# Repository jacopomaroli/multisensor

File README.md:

# Multisensor
This is a domotic project aimed to detect presence, temperature and light level in a room and share data with the rest of the ecosystem (e.g. homeassistant)

# Notes
VDO/CS of BME680 should be connected to GND
https://github.com/esphome/issues/issues/2421

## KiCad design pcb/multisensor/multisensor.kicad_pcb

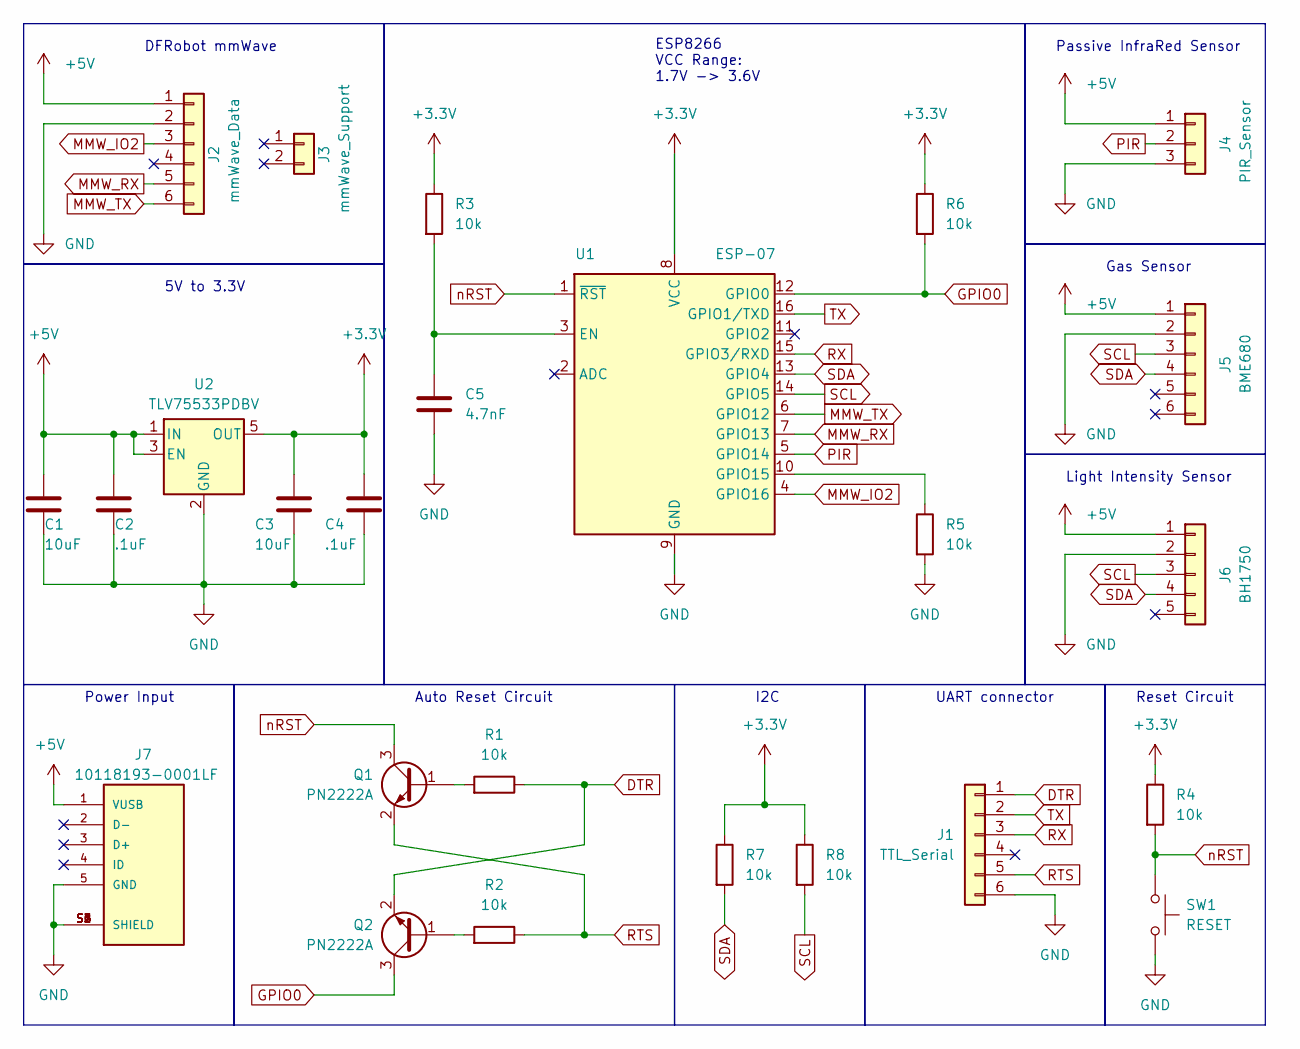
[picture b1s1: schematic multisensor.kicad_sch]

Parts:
C1, C3: 10uF; C_1206_3216Metric; MPN CL31B106KAHNNNE
C2, C4: .1uF; C_1206_3216Metric; MPN C1206C104K5RAC7800
C5: 4.7nF; C_1206_3216Metric; MPN KGM31TR72D472KU
J1: TTL_Serial; PinSocket_1x06_P2.54mm_Vertical; MPN PPPC061LFBN-RC
J2: mmWave_Data; PinSocket_1x06_P2.54mm_Vertical; MPN PPPC061LFBN-RC
J3: mmWave_Support; PinSocket_1x02_P2.54mm_Vertical; MPN PPPC021LFBN-RC
J4: PIR_Sensor; PinSocket_1x03_P2.54mm_Vertical; MPN PPPC031LFBN-RC
J5: BME680; PinSocket_1x06_P2.54mm_Horizontal; MPN PPPC061LGBN-RC
J6: BH1750; PinSocket_1x05_P2.54mm_Horizontal; MPN PPPC051LGBN-RC
J7: 10118193-0001LF; AMPHENOL_10118193-0001LF; PARTREV E; DigiKey_Part_Number 609-4616-2-ND
Q1, Q2: PN2222A; SOT-23; MPN MMBT2222A-TP
R1, R2, R3, R4, R5, R6, R7, R8: 10k; R_0805_2012Metric; MPN RMCF0805FT10K0
SW1: RESET; SW_PUSH_6mm; MPN TS02-66-60-BK-160-LCR-D
U1: ESP-07; MPN ESP-07
U2: TLV75533PDBV; SOT-23-5; MPN TLV75533PDBVR

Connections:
+3.3V: C3.1, C4.1, R3.1, R4.1, R6.1, R7.1, R8.1, U1.8 (VCC), U2.5 (OUT)
+5V: C1.1, C2.1, J2.1, J4.1, J5.1, J6.1, J7.1 (VUSB), U2.1 (IN), U2.3 (EN)
DTR: J1.1, Q2.2 (E), R1.1
GND: C1.2, C2.2, C3.2, C4.2, C5.2, J1.6, J2.2, J4.3, J5.2, J6.2, J7.5 (GND), J7.S1 (SHIELD), J7.S2 (SHIELD), J7.S3 (SHIELD), J7.S4 (SHIELD), J7.S5 (SHIELD), J7.S6 (SHIELD), R5.2, SW1.2, U1.9 (GND), U2.2 (GND)
GPIO0: Q2.3 (C), R6.2, U1.12 (GPIO0)
MMW_IO2: J2.3, U1.4 (GPIO16)
MMW_RX: J2.5, U1.7 (GPIO13)
MMW_TX: J2.6, U1.6 (GPIO12)
unnamed: Q1.1 (B), R1.2
unnamed: Q2.1 (B), R2.2
unnamed: C5.1, R3.2, U1.3 (EN)
unnamed: R5.1, U1.10 (GPIO15)
PIR: J4.2, U1.5 (GPIO14)
RTS: J1.5, Q1.2 (E), R2.1
RX: J1.3, U1.15 (GPIO3/RXD)
SCL: J5.3, J6.3, R8.2, U1.14 (GPIO5)
SDA: J5.4, J6.4, R7.2, U1.13 (GPIO4)
TX: J1.2, U1.16 (GPIO1/TXD)
nRST: Q1.3 (C), R4.2, SW1.1, U1.1 (~RST)

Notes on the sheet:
Light Intensity Sensor
DFRobot mmWave
Auto Reset Circuit
Reset Circuit
ESP8266 VCC Range: 1.7V -> 3.6V
Gas Sensor
Power Input
Passive InfraRed Sensor
UART connector
I2C
5V to 3.3V

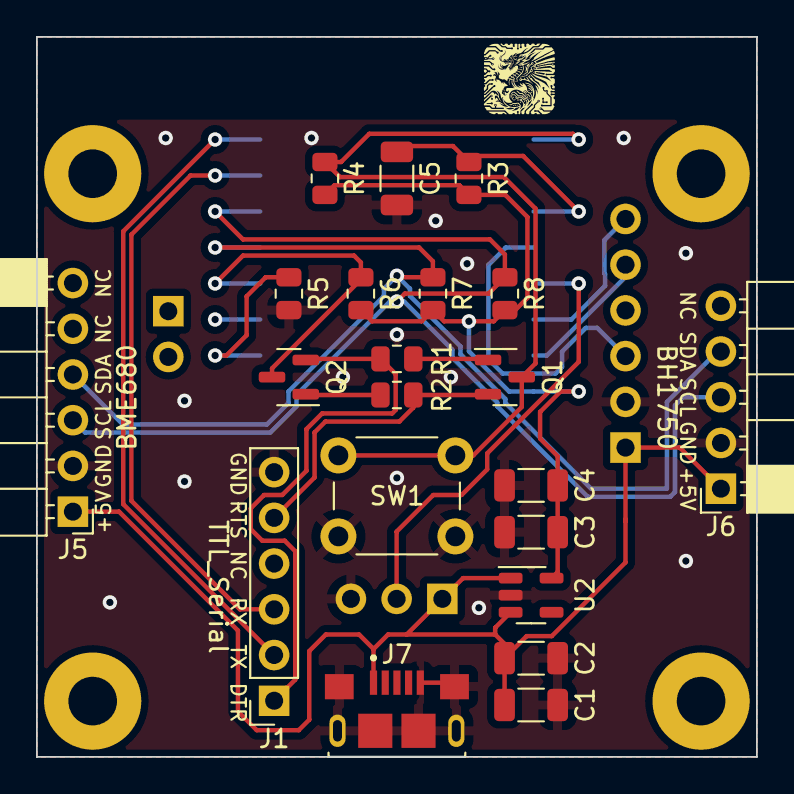
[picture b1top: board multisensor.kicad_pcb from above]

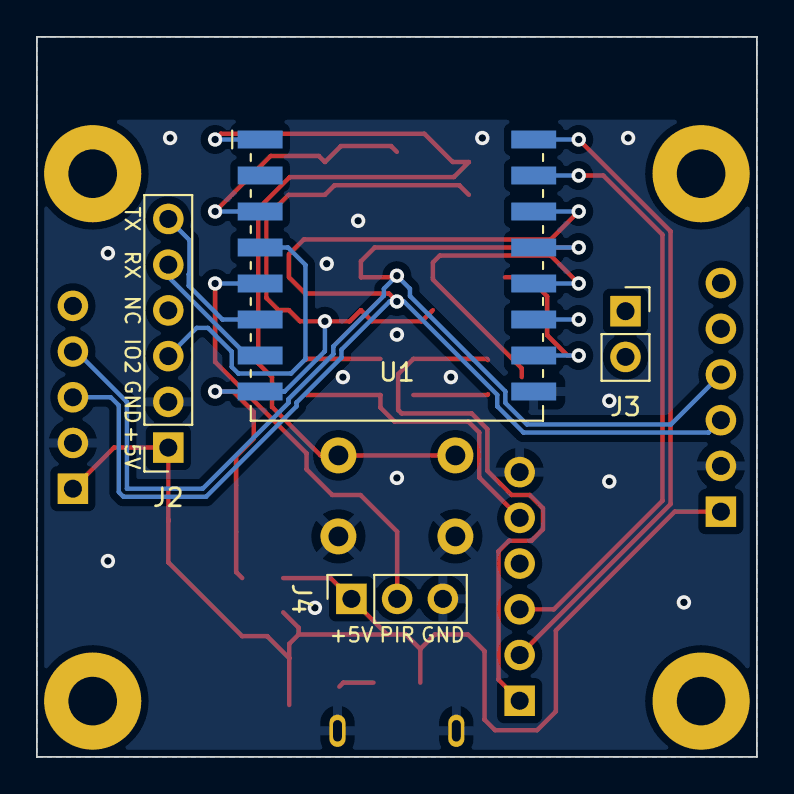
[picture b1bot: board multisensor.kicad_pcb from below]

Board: 2 copper layers, 40.0 x 40.0 mm, 25 parts (4 on the bottom side), 19 nets.

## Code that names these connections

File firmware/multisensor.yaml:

substitutions:
  device_name: occup-light-gas-sensor
  device_name_pretty: Multi Sensor
  # temperature sensor SCL pin - - this must be linked to the SCL pin of the BME680 sensor
  scl_pin: GPIO5
  # temperature sensor SDA pin - this must be linked to the SDA pin of the BME680 sensor
  sda_pin: GPIO4
  # UART Pin configured for mmWave sensor
  uart_tx_pin: GPIO12
  # TX Pin configured for mmWave sensor - this must be linked to the RX Pin on the radar
  uart_rx_pin: GPIO13
  # TX Pin configured for mmWave sensor - this must be linked to the TX Pin on the radar
  gpio_pin: GPIO16
  # PIR sensor pin
  pir_pin: GPIO14

# include the yml file with the radar code and configuration
packages:
  inclusions: !include packages/leapmmw_sensor.yml

esphome:
  name: $device_name

# esp8266:
#   board: d1_mini

esp8266:
   board: esp07

# esp32:
#   board: wemos_d1_mini32
#   framework:
#     type: arduino

# Enable logging
logger:

# Enable Home Assistant API
api:
  password: ""

ota:
  password: ""

wifi:
  ssid: !secret wifi_ssid
  password: !secret wifi_password

  # Enable fallback hotspot (captive portal) in case wifi connection fails
  ap:
    ssid: "${device_name_pretty}"
    password: !secret wifi_password

#captive_portal:

web_server:
 port: 80
 version: 2
 include_internal: true

binary_sensor:
  - platform: gpio
    pin: ${pir_pin}
    name: "PIR Sensor"
    device_class: motion

i2c:
  sda: ${sda_pin}
  scl: ${scl_pin}
  
bme680_bsec:
  address: 0x76
  sample_rate: lp
  state_save_interval: 1h
  #temperature_offset: 1.42  #(calibration without mmWave radar & v2 case version)
  #temperature_offset: 1.81  #(calibrated without mmWave radar & v1 case version)
  temperature_offset: 2.48   #(calibration with mmWave radar & v1 case version)

sensor:
  - platform: bh1750  #illuminance sensor
    name: "${device_name_pretty} Illuminance"
    address: 0x23
    update_interval: 10s

  - platform: bme680_bsec
    temperature:
      # Temperature in °C
      name: "${device_name_pretty} Temperature"
      sample_rate: lp
      accuracy_decimals: 2
      filters:
        - sliding_window_moving_average:
            window_size: 20
            send_every: 20  
    pressure:
      name: "${device_name_pretty} Pressure"
      sample_rate: lp
      filters:
        - median
    humidity:
      name: "${device_name_pretty} Humidity"
      sample_rate: lp
      filters:
        - median
    gas_resistance:
      name: "${device_name_pretty} Gas Resistance"
      filters:
        - median
    iaq:
      name: "${device_name_pretty} IAQ"
      id: iaq
      filters:
        - median
    iaq_accuracy:
      name: "${device_name_pretty} IAQ Accuracy"
    co2_equivalent:
      name: "${device_name_pretty} CO2 Equivalent"
      filters:
        - median
    breath_voc_equivalent:
      name: "${device_name_pretty} Breath VOC Equivalent"
      filters:
        - median

text_sensor:
  - platform: bme680_bsec
    iaq_accuracy:
      name: "${device_name_pretty} IAQ Accuracy"
  - platform: template
    name: "${device_name_pretty} Air Quality"
    icon: "mdi:checkbox-marked-circle-outline"
    lambda: |-
      if ( int(id(iaq).state) <= 50) {
        return {"Excellent"};
      }
      else if (int(id(iaq).state) >= 51 && int(id(iaq).state) <= 100) {
        return {"Good"};
      }
      else if (int(id(iaq).state) >= 101 && int(id(iaq).state) <= 150) {
        return {"Lightly polluted"};
      }
      else if (int(id(iaq).state) >= 151 && int(id(iaq).state) <= 200) {
        return {"Moderately polluted"};
      }
      else if (int(id(iaq).state) >= 201 && int(id(iaq).state) <= 250) {
        return {"Heavily polluted"};
      }
      else if (int(id(iaq).state) >= 251 && int(id(iaq).state) <= 350) {
        return {"Severely polluted"};
      }
      else if (int(id(iaq).state) >= 351) {
        return {"Extremely polluted"};
      }
      else {
        return {"error"};
      }

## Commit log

2023-10-22 initial
2023-10-22 add mmwave model
2023-10-22 remove file
2023-10-22 fix gitignore
2023-10-22 update esp-7 model
2023-10-22 improve pir model
2023-10-26 fix vcc/gnd pointing up/down
2023-10-26 board images
2023-11-23 add tantalum caps to VCC
2023-11-24 update prj_img
2023-11-26 add filtering caps + external pullups
2023-11-30 upadate regulator and connector
2023-12-05 add spice simulations and manufacturing files
2023-12-05 update gerber files
2023-12-05 update gerber output path
2023-12-28 fix pcb layout
2024-01-05 finalize v0.2.0
2024-01-07 add notes
